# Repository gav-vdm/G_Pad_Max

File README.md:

# G_Pad_Max

# BOM:
- 8x Cherry MX switches
- 1x EC11 Encoder
- 1x PCB
- 9x Through-hole 1N4148 Diodes
- 16x SK6812 MINI-E LEDs
- 1x 0.91 inch OLED displays
- 8x Blank DSA keycaps
- 1x Seeed XIAO RP2040
- 1x 3D PRINTED CASE
# Images 
- 
- 
- 
- 

# Info
I want to make a few iterations on the case when I physically have the PCB so for now it is just temporary to get the sizing right. 

I also need to review the firmware when I assemble the pcb. 

# Extra
- There is a option to add a level switcher to make the signalling better for the LEDs but for now I'm just going to bridge the pads and skip it.

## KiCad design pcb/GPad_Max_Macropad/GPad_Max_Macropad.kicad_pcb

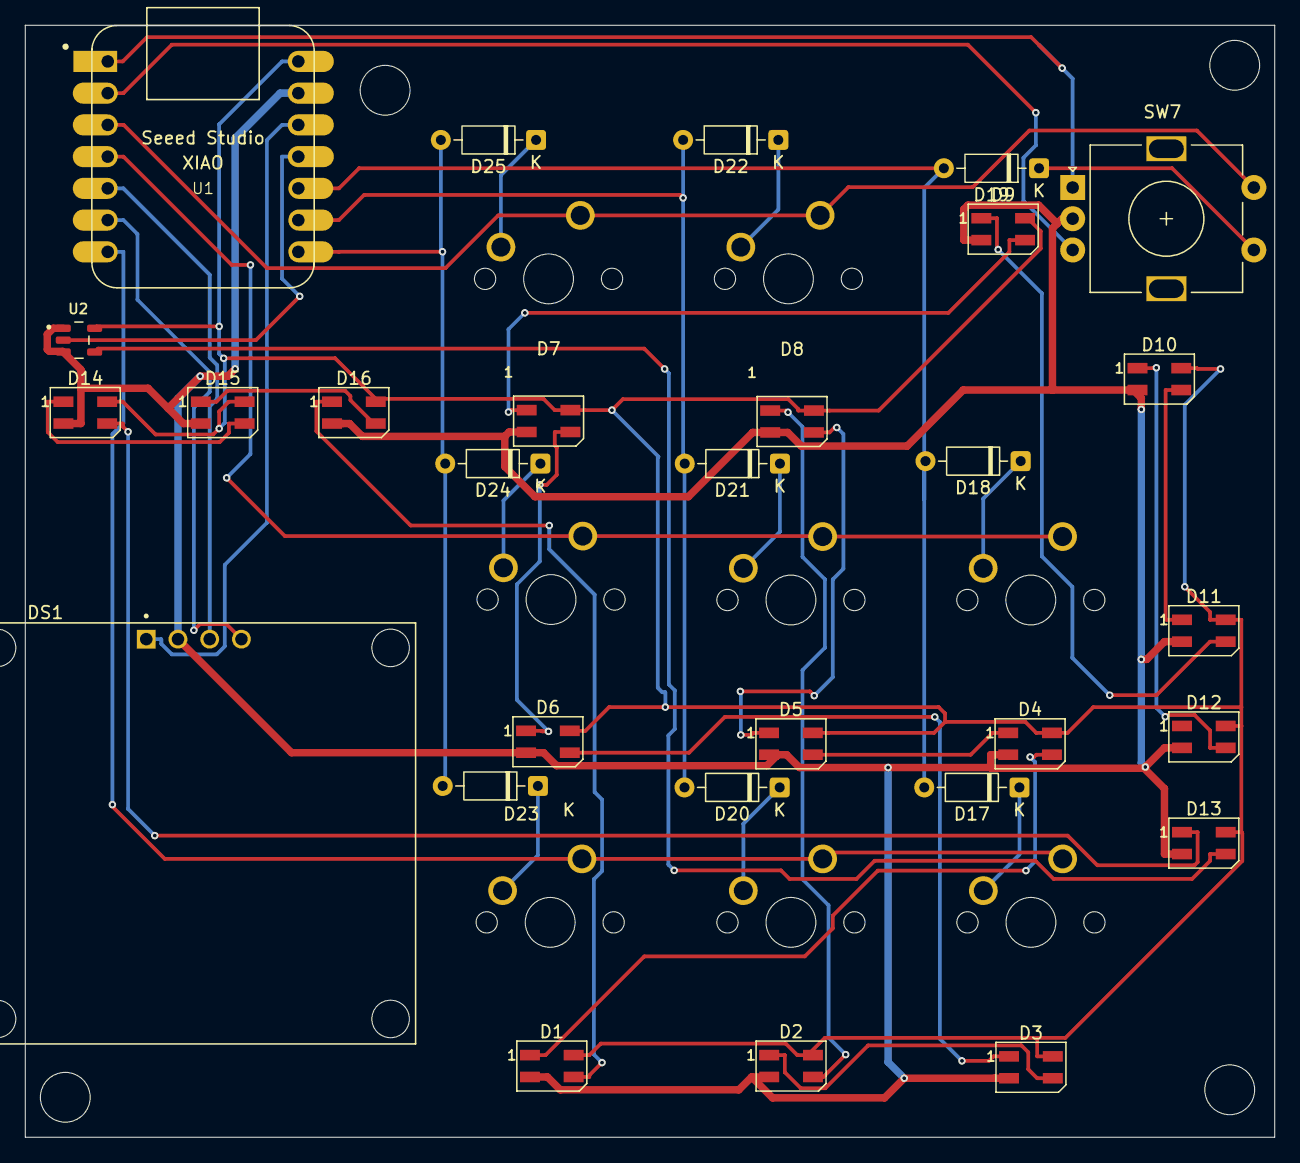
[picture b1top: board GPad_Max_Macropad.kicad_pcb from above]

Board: 2 copper layers, 100.0 x 89.0 mm, 37 parts (0 on the bottom side), 39 nets.

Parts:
D1, D2, D3, D4, D5, D6, D7, D8, D9, D10, D11, D12, D13, D14, D15, D16: SK6812MINI; LED_SK6812MINI_PLCC4_3.5x3.5mm_P1.75mm
D17, D18, D19, D20, D21, D22, D23, D24, D25: 1N4148; D_DO-35_SOD27_P7.62mm_Horizontal
DS1: OLED_128X64_1.3_I2C; LCD_OLED_128X64_1.3_I2C
SW1, SW2, SW3, SW4, SW5, SW6, SW8, SW9: SW_Push; MX-Solderable-1U
SW7: RotaryEncoder_Switch; RotaryEncoder_Alps_EC11E-Switch_Vertical_H20mm
U1: XIAO-RP2040-DIP; XIAO-Generic-Hybrid-14P-2.54-21X17.8MM
U2: SN74AHCT1G125DBVR; SOT95P280X145-5N

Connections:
-3V3: DS1.1 (VDD), U1.12 (3V3)
/COL0: SW1.2, SW2.2, SW3.2, U1.7 (GPIO0/TX)
/COL1: SW4.2, SW5.2, SW6.2, U1.4 (GPIO29/ADC3/A3)
/COL2: SW7.S2, SW8.2, SW9.2, U1.3 (GPIO28/ADC2/A2)
/ENC_A: SW7.A, U1.1 (GPIO26/ADC0/A0)
/ENC_B: SW7.B, U1.2 (GPIO27/ADC1/A1)
/LED_DATA: U1.11 (GPIO3/MOSI), U2.2 (A)
/LED_DIN: D13.3 (DIN), U2.4 (Y)
/ROW0: D17.2 (A), D18.2 (A), D19.2 (A), U1.10 (GPIO4/MISO)
/ROW1: D20.2 (A), D21.2 (A), D22.2 (A), U1.9 (GPIO2/SCK)
/ROW2: D23.2 (A), D24.2 (A), D25.2 (A), U1.8 (GPIO1/RX)
GND: D1.2 (VSS), D2.2 (VSS), D3.2 (VSS), D4.2 (VSS), D5.2 (VSS), D6.2 (VSS), D7.2 (VSS), D8.2 (VSS), D9.2 (VSS), D10.2 (VSS), D11.2 (VSS), D12.2 (VSS), D13.2 (VSS), D14.2 (VSS), D15.2 (VSS), D16.2 (VSS), DS1.2 (GND), SW7.C, U1.13 (GND), U2.1 (~OE), U2.3 (GND)
unnamed: D1.3 (DIN), D16.1 (DOUT)
unnamed: D1.1 (DOUT), D4.3 (DIN)
unnamed: D2.3 (DIN), D8.1 (DOUT)
unnamed: D2.1 (DOUT), D3.3 (DIN)
unnamed: D3.1 (DOUT), D6.3 (DIN)
unnamed: D4.1 (DOUT), D5.3 (DIN)
unnamed: D5.1 (DOUT), D8.3 (DIN)
unnamed: D6.1 (DOUT), D7.3 (DIN)
unnamed: D7.1 (DOUT), D9.3 (DIN)
unnamed: D10.3 (DIN), D11.1 (DOUT)
unnamed: D10.1 (DOUT), D12.3 (DIN)
unnamed: D9.1 (DOUT), D11.3 (DIN)
unnamed: D13.1 (DOUT), D14.3 (DIN)
unnamed: D14.1 (DOUT), D15.3 (DIN)
unnamed: D15.1 (DOUT), D16.3 (DIN)
unnamed: D17.1 (K), SW1.1
unnamed: D18.1 (K), SW4.1
unnamed: D19.1 (K), SW7.S1
unnamed: D20.1 (K), SW2.1
unnamed: D21.1 (K), SW5.1
unnamed: D22.1 (K), SW8.1
unnamed: D23.1 (K), SW3.1
unnamed: D24.1 (K), SW6.1
unnamed: D25.1 (K), SW9.1
unnamed: DS1.3 (SCK), U1.5 (GPIO6/SDA)
unnamed: DS1.4 (SDA), U1.6 (GPIO7/SCL)
VBUS: D1.4 (VDD), D2.4 (VDD), D3.4 (VDD), D4.4 (VDD), D5.4 (VDD), D6.4 (VDD), D7.4 (VDD), D8.4 (VDD), D9.4 (VDD), D10.4 (VDD), D11.4 (VDD), D12.4 (VDD), D13.4 (VDD), D14.4 (VDD), D15.4 (VDD), D16.4 (VDD), U1.14 (VBUS), U2.5 (VCC)

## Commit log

2025-12-30 Final commit
2025-12-30 Replace image filenames with links in README
    Updated image references in README to use links.
2025-12-31 Fix image links and typo in README
    Updated image links to use markdown format and corrected a typo in the header.
2026-01-04 WIP on main
2026-01-04 Fix typo in header from 'Inf' to 'Info'
2026-01-06 Add new image to README
    Added an additional image to the README.
